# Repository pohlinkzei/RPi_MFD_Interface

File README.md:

# RPi_MFD_Interface
Interface between RaspberryPi and VW MFD Radio Navigation System

The RPi_MFD_Interface is a Atmega16-based device to connect the
RaspberryPi with the CarAudio head unit. Its main purpose is to read the
buttons of the car audio and send it to the pi.  The second purpose is
to power the pi with control over booting up and shutting down of the
raspberry pi to prevent it killing the cars battery.

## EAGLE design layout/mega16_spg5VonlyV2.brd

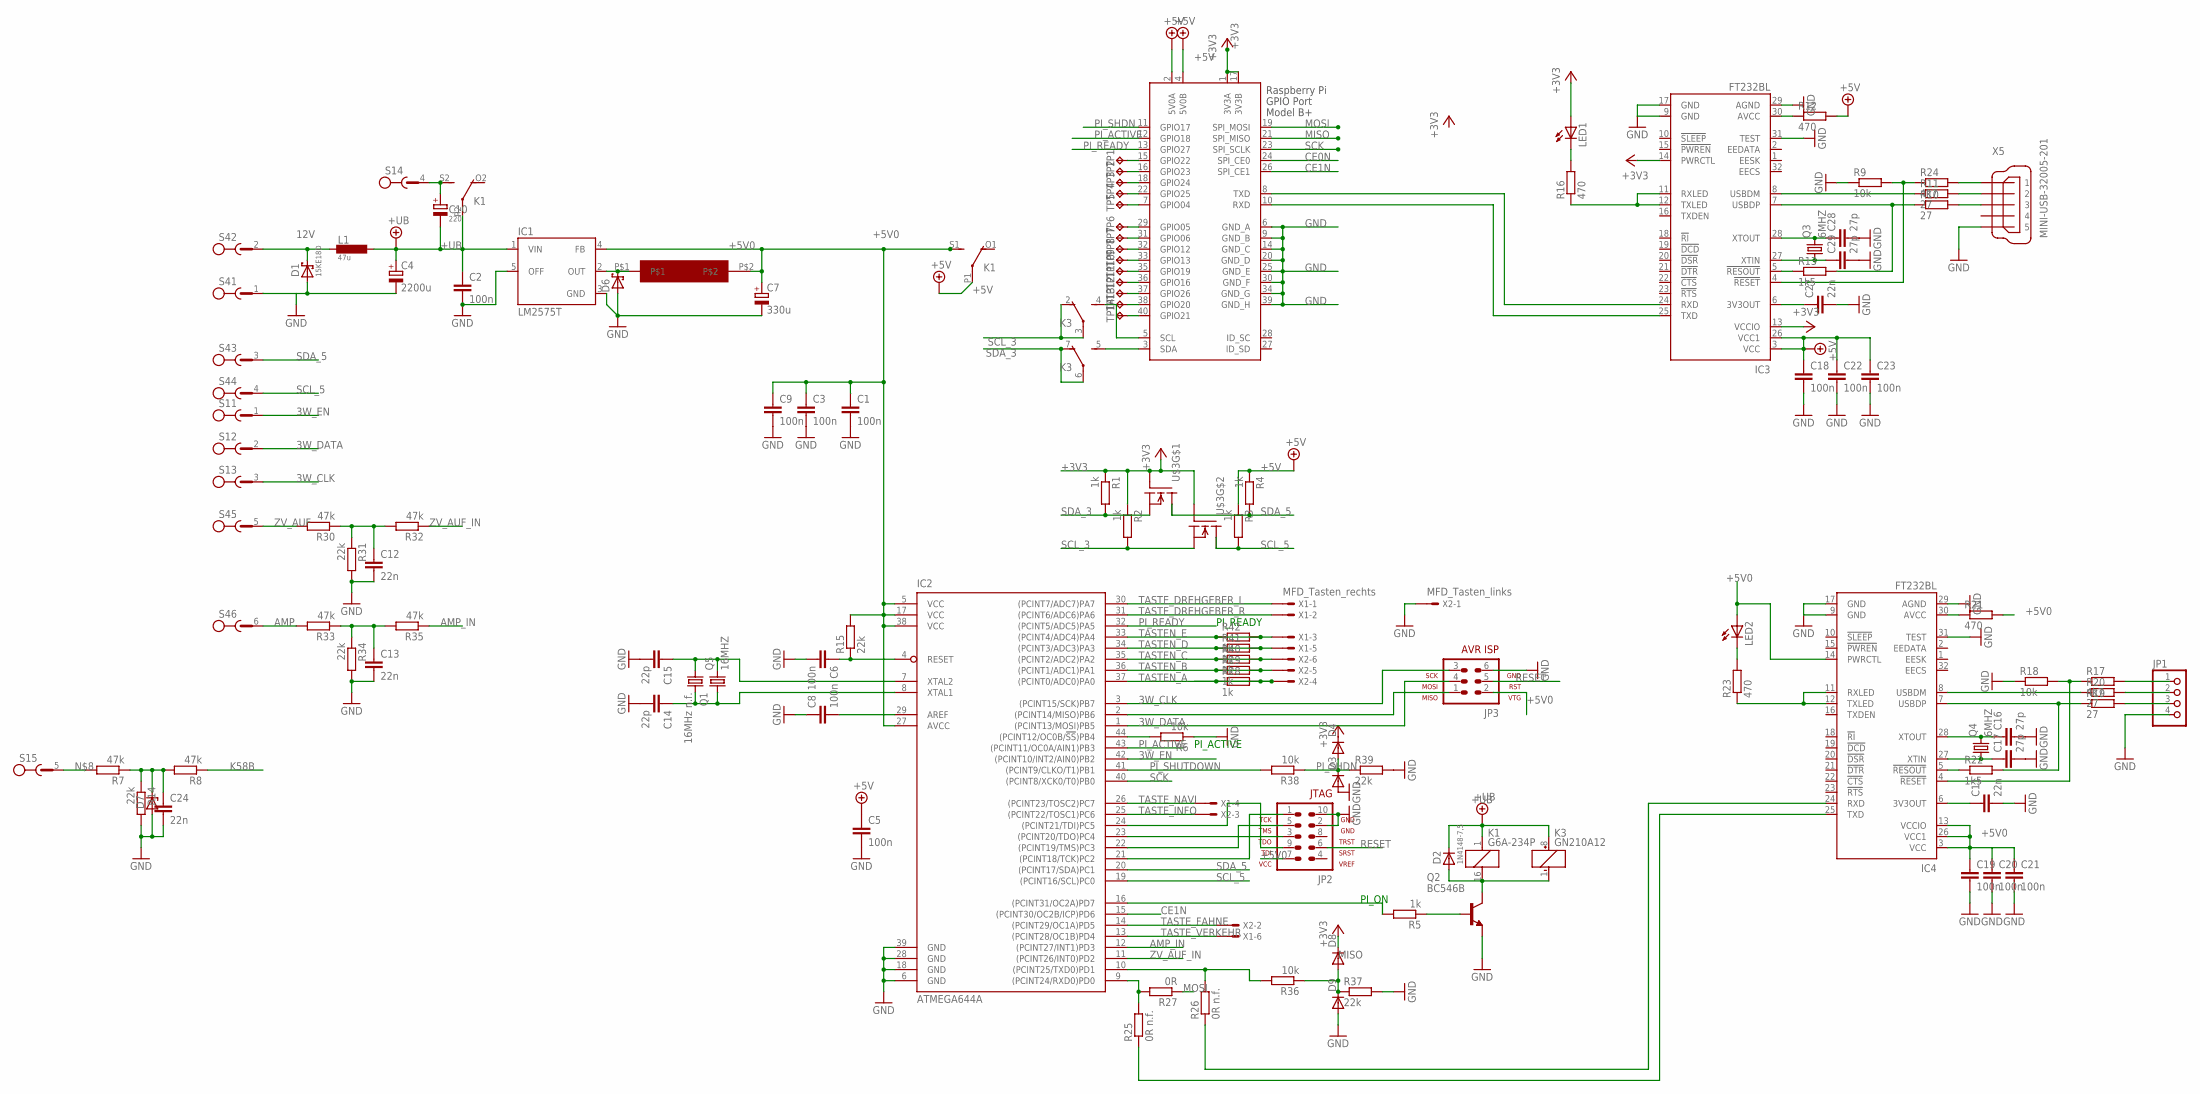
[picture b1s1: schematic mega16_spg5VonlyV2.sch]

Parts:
C1, C2, C3, C5, C6, C8, C9, C18, C19, C20, C21, C22, C23: 100n; C1206
C4: 2200u; E5-10,5
C7: 330u; E5-10,5
C10: 220; E2.5-5
C11, C12, C13, C24, C27: 22n; C1206
C14, C15: 22p; C1206
C16, C17, C28, C29: 27p; C1206
D1: 15KE18D; DO201T15
D2: 1N4148-7,5; DO35-7,5
D3, D4, D8, D9: DIODE-MICROMELF-W; MICROMELF-W
D6: SCHOTTKY-DIODEF126Z12; F126Z12
D7: ZPP-7.5; DO35-7,5
IC1: LM2575T; TO220-5
IC2: ATMEGA644A; TQFP44
IC3, IC4: FT232BL; LQFP32-7X7
JP1: PINHD-1X4_2.54; 1X04
JP2: AVR-JTAG-10
JP3: AVR-ISP-6
K1: G6A-234P
K3: GN210A12; GN-A
L1: 47u; MESC26
LED1, LED2: LEDP-LCC-2; P-LCC-2
Q1: 16MHz n.f.; HC49/S
Q2: BC546B; TO92-EBC
Q3, Q4: 6MHZ; CTS406
Q5: 16MHZ; CTS406
R1, R2, R3, R4, R5, R28, R29, R40, R41, R42: 1k; M1206
R6, R9, R18, R36, R38: 10k; M1206
R7, R8, R30, R32, R33, R35: 47k; M1206
R10, R11, R19, R20: 27; M1206
R12, R16, R21, R23: 470; M1206
R13, R22: 1k5; M1206
R14, R15, R31, R34, R37: 22k; M1206
R17, R24: 4k7; M1206
R25, R26: 0R n.f.; M1206
R27: 0R; M1206
R39: 22k; R1206
S1: CON-RIA-183-05; RIA-183-05
S4: CON-RIA-183-06; RIA-183-06
TP1, TP2, TP3, TP4, TP5, TP6, TP7, TP8, TP9, TP10, TP11, TP12, TP13, TP14: TPPAD1-13; P1-13
U$1: PISR
U$3: IRF7103; SO-8
X1: MFD_Tasten_rechts; 057-006-1
X2: MFD_Tasten_links; 057-006-1
X3: RASPI_GPIO_B+#_PIN; RASPI_GPIO_B+_PIN
X5: MINI-USB-32005-201; 32005-201

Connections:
3W_CLK: IC2.3 ((PCINT15/SCK)PB7), JP3.3, S1.3
3W_DATA: IC2.1 ((PCINT13/MOSI)PB5), JP3.4, S1.2
3W_EN: IC2.42 ((PCINT10/INT2/AIN0)PB2), S1.1
12V: D1.C, L1.1, S4.2
+3V3: D4.C, D8.C, IC3.13 (VCCIO), IC3.14 (PWRCTL), LED1.A, R1.1, R2.1, U$3.2 (G), U$3.4 (G), X3.1 (3V3A), X3.17 (3V3B)
+5V: C5.1, C18.1, C22.1, C23.1, IC3.3 (VCC), IC3.26 (VCC1), K1.P1, R3.1, R4.1, R12.2, X3.2 (5V0A), X3.4 (5V0B)
+5V0: C1.1, C3.1, C7.+, C9.1, C19.1, C20.1, C21.1, IC1.4 (FB), IC2.5 (VCC), IC2.17 (VCC), IC2.27 (AVCC), IC2.38 (VCC), IC4.3 (VCC), IC4.13 (VCCIO), IC4.14 (PWRCTL), IC4.26 (VCC1), JP2.7, JP3.2, K1.S1 (S), LED2.A, R15.2, R21.2, U$1.P$2
+UB: C2.1, C4.+, C10.-, D2.C, IC1.1 (VIN), K1.1, K1.P2, K3.8 (+), L1.2
AMP: R33.2, S4.6
AMP_IN: IC2.12 ((PCINT27/INT1)PD3), R35.1
CE0N: X3.24 (SPI_CE0)
CE1N: IC2.15 ((PCINT30/OC2B/ICP)PD6), X3.26 (SPI_CE1)
GND: C1.2, C2.2, C3.2, C4.-, C5.2, C6.2, C7.-, C8.1, C9.2, C11.2, C12.2, C13.2, C14.2, C15.2, C16.2, C17.2, C18.2, C19.2, C20.2, C21.2, C22.2, C23.2, C24.2, C27.2, C28.2, C29.2, D1.A, D3.A, D6.A, D7.A, D9.A, IC1.3 (GND), IC1.5 (OFF), IC2.6 (GND), IC2.18 (GND), IC2.28 (GND), IC2.39 (GND), IC3.9 (GND), IC3.17 (GND), IC3.29 (AGND), IC3.31 (TEST), IC4.9 (GND), IC4.17 (GND), IC4.29 (AGND), IC4.31 (TEST), JP1.4, JP2.2, JP2.10, JP3.6, Q2.E, R6.1, R9.1, R14.2, R18.1, R31.2, R34.2, R37.2, R39.2, S4.1, X2.1, X3.6 (GND_A), X3.9 (GND_B), X3.14 (GND_C), X3.20 (GND_D), X3.25 (GND_E), X3.30 (GND_F), X3.34 (GND_G), X3.39 (GND_H), X5.5
K58B: R8.1
MISO: D8.A, D9.C, R36.1, R37.1, X3.21 (SPI_MISO)
MOSI: R27.1, X3.19 (SPI_MOSI)
unnamed: C10.+, K1.S2 (S), S1.4
unnamed: D2.A, K1.16 (2), K3.1 (-), Q2.C
unnamed: IC3.24 (RXD), X3.8 (TXD)
unnamed: C24.1, D7.C, R7.1, R8.2, R14.1
unnamed: D6.C, IC1.2 (OUT), U$1.P$1
unnamed: C15.1, IC2.7 (XTAL2), Q1.1, Q5.3 (2)
unnamed: C8.2, IC2.29 (AREF)
unnamed: R7.2, S1.5
unnamed: IC3.25 (TXD), X3.10 (RXD)
unnamed: IC2.10 ((PCINT25/TXD0)PD1), R26.2, R36.2
unnamed: IC2.21 ((PCINT18/TCK)PC2), JP2.1
unnamed: IC2.22 ((PCINT19/TMS)PC3), JP2.5
unnamed: Q2.B, R5.1
unnamed: IC2.44 ((PCINT12/OC0B/!SS!)PB4), R6.2
unnamed: IC2.23 ((PCINT20/TDO)PC4), JP2.3
unnamed: IC2.16 ((PCINT31/OC2A)PD7), R5.2
unnamed: IC2.24 ((PCINT21/TDI)PC5), JP2.9
unnamed: C11.1, IC4.6 (3V3OUT)
unnamed: IC3.11 (RXLED), IC3.12 (TXLED), R16.1
unnamed: IC2.2 ((PCINT14/MISO)PB6), JP3.1
unnamed: LED1.C, R16.2
unnamed: IC4.7 (USBDP), R19.1, R22.2
unnamed: IC4.8 (USBDM), R20.1
unnamed: JP1.1, R17.2
unnamed: IC4.4 (!RESET), R17.1, R18.2
unnamed: JP1.3, R19.2
unnamed: JP1.2, R20.2
unnamed: IC4.30 (AVCC), R21.1
unnamed: IC4.5 (!RESOUT), R22.1
unnamed: C17.1, IC4.27 (XTIN), Q4.1
unnamed: C16.1, IC4.28 (XTOUT), Q4.3 (2)
unnamed: IC4.24 (RXD), R26.1
unnamed: IC4.25 (TXD), R25.1
unnamed: IC4.11 (RXLED), IC4.12 (TXLED), R23.1
unnamed: LED2.C, R23.2
unnamed: IC2.9 ((PCINT24/RXD0)PD0), R25.2, R27.2
unnamed: K3.5 (S), X3.3 (SDA)
unnamed: TP14.1, X3.40 (GPIO21)
unnamed: K3.4 (S), X3.5 (SCL)
unnamed: TP13.1, X3.38 (GPIO20)
unnamed: TP12.1, X3.37 (GPIO26)
unnamed: TP11.1, X3.36 (GPIO16)
unnamed: TP10.1, X3.35 (GPIO19)
unnamed: TP9.1, X3.33 (GPIO13)
unnamed: C14.1, IC2.8 (XTAL1), Q1.2, Q5.1
unnamed: TP8.1, X3.32 (GPIO12)
unnamed: TP7.1, X3.31 (GPIO06)
unnamed: TP6.1, X3.29 (GPIO05)
unnamed: TP1.1, X3.15 (GPIO22)
unnamed: C12.1, R30.1, R31.1, R32.2
unnamed: TP2.1, X3.16 (GPIO23)
unnamed: C13.1, R33.1, R34.1, R35.2
unnamed: TP3.1, X3.18 (GPIO24)
unnamed: R10.2, X5.3
unnamed: R11.2, X5.2
unnamed: IC3.30 (AVCC), R12.1
unnamed: IC3.5 (!RESOUT), R13.1
unnamed: C27.1, IC3.6 (3V3OUT)
unnamed: IC3.7 (USBDP), R10.1, R13.2
unnamed: IC3.8 (USBDM), R11.1
unnamed: R24.2, X5.1
unnamed: IC3.4 (!RESET), R9.2, R24.1
unnamed: C29.1, IC3.27 (XTIN), Q3.1
unnamed: C28.1, IC3.28 (XTOUT), Q3.3 (2)
unnamed: TP4.1, X3.22 (GPIO25)
unnamed: TP5.1, X3.7 (GPIO04)
PI_ACTIVE: IC2.43 ((PCINT11/OC0A/AIN1)PB3), X3.12 (GPIO18)
PI_READY: IC2.32 ((PCINT5/ADC5)PA5), X3.13 (GPIO27)
PI_SHDN: D3.C, D4.A, R38.1, R39.1, X3.11 (GPIO17)
PI_SHUTDOWN: IC2.41 ((PCINT9/CLKO/T1)PB1), R38.2
RESET: C6.1, IC2.4 (RESET), JP2.6, JP3.5, R15.1
SCK: IC2.40 ((PCINT8/XCK0/T0)PB0), X3.23 (SPI_SCLK)
SCL_3: K3.2 (O), K3.3, R2.2, U$3.3 (S)
SCL_5: IC2.19 ((PCINT16/SCL)PC0), R3.2, S4.4, U$3.5 (D1), U$3.6 (D)
SDA_3: K3.6, K3.7 (O), R1.2, U$3.1 (S)
SDA_5: IC2.20 ((PCINT17/SDA)PC1), R4.2, S4.3, U$3.7 (D), U$3.8 (D1)
TASTEN_A: IC2.37 ((PCINT0/ADC0)PA0), R28.1, R28.2, X2.4
TASTEN_B: IC2.36 ((PCINT1/ADC1)PA1), R29.1, R29.2, X2.5
TASTEN_C: IC2.35 ((PCINT2/ADC2)PA2), R40.1, R40.2, X2.6
TASTEN_D: IC2.34 ((PCINT3/ADC3)PA3), R41.1, R41.2, X1.5
TASTEN_E: IC2.33 ((PCINT4/ADC4)PA4), R42.1, R42.2, X1.3
TASTE_DREHGEBER_L: IC2.30 ((PCINT7/ADC7)PA7), X1.1
TASTE_DREHGEBER_R: IC2.31 ((PCINT6/ADC6)PA6), X1.2
TASTE_FAHNE: IC2.14 ((PCINT29/OC1A)PD5), X2.2
TASTE_INFO: IC2.25 ((PCINT22/TOSC1)PC6), X2.3
TASTE_NAVI: IC2.26 ((PCINT23/TOSC2)PC7), X1.4
TASTE_VERKEHR: IC2.13 ((PCINT28/OC1B)PD4), X1.6
ZV_AUF: R30.2, S4.5
ZV_AUF_IN: IC2.11 ((PCINT26/INT0)PD2), R32.1

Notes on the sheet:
PI_ACTIVE
PI_ON
PI_READY

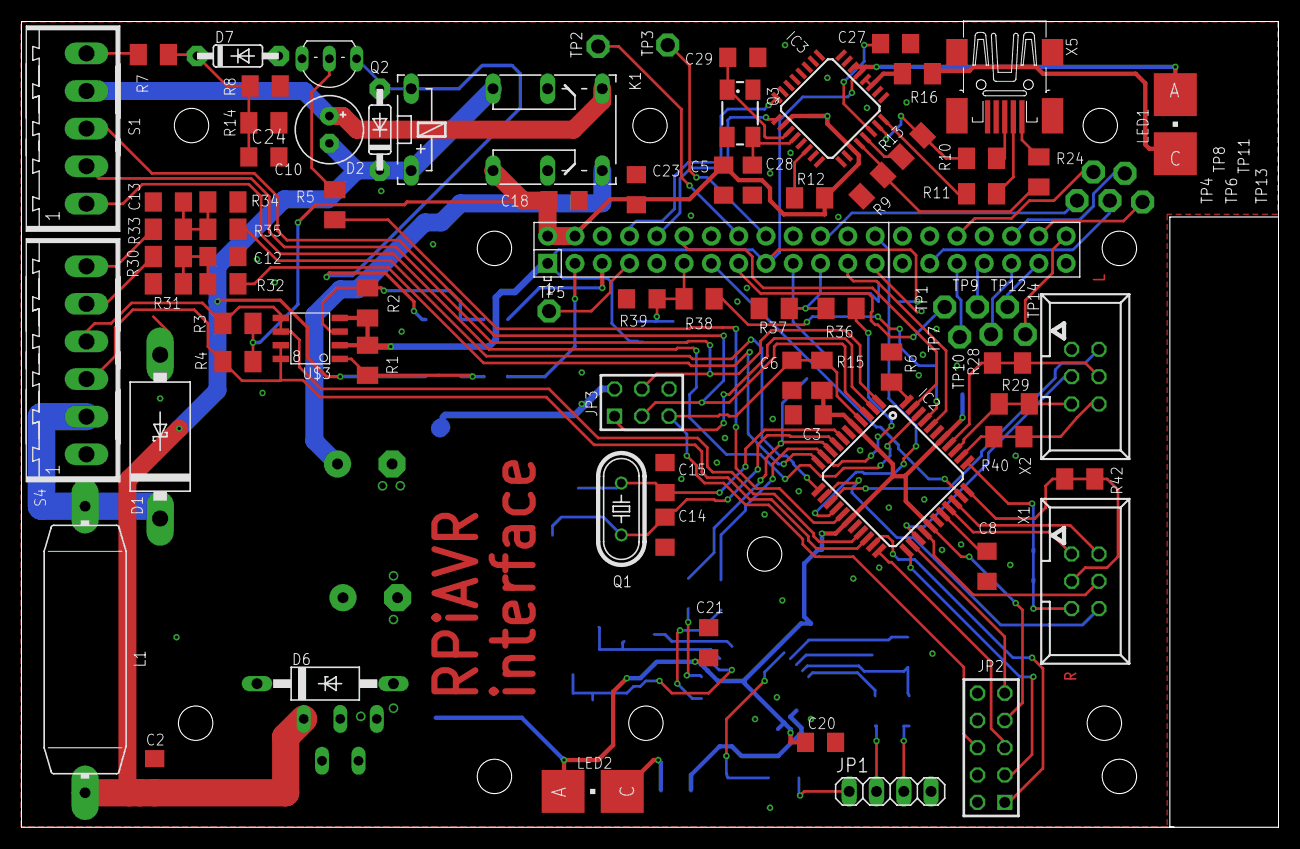
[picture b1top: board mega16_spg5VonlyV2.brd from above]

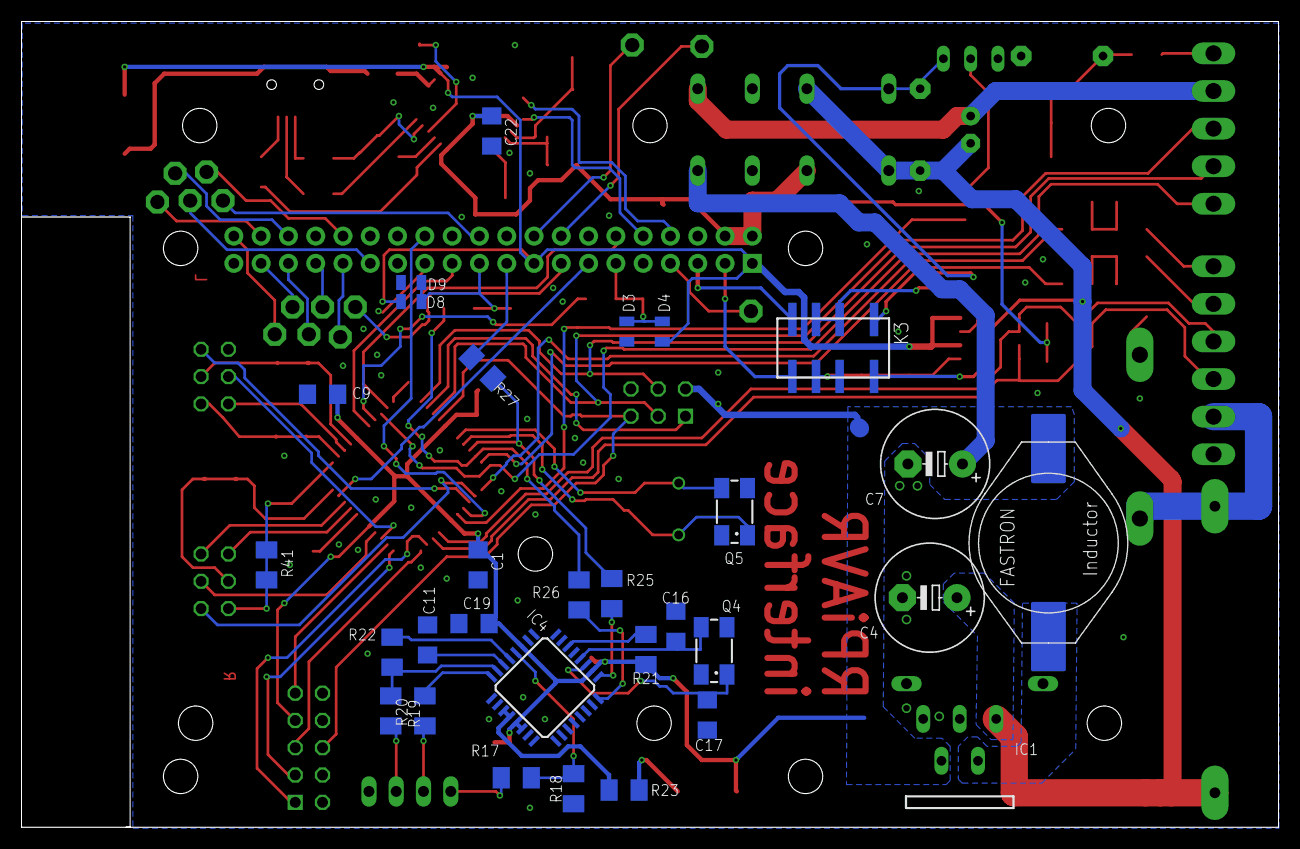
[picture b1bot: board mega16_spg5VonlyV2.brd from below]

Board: 2 copper layers, 117.0 x 75.0 mm, 117 parts (30 on the bottom side), 103 nets.

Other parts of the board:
U$2: EUROBOX

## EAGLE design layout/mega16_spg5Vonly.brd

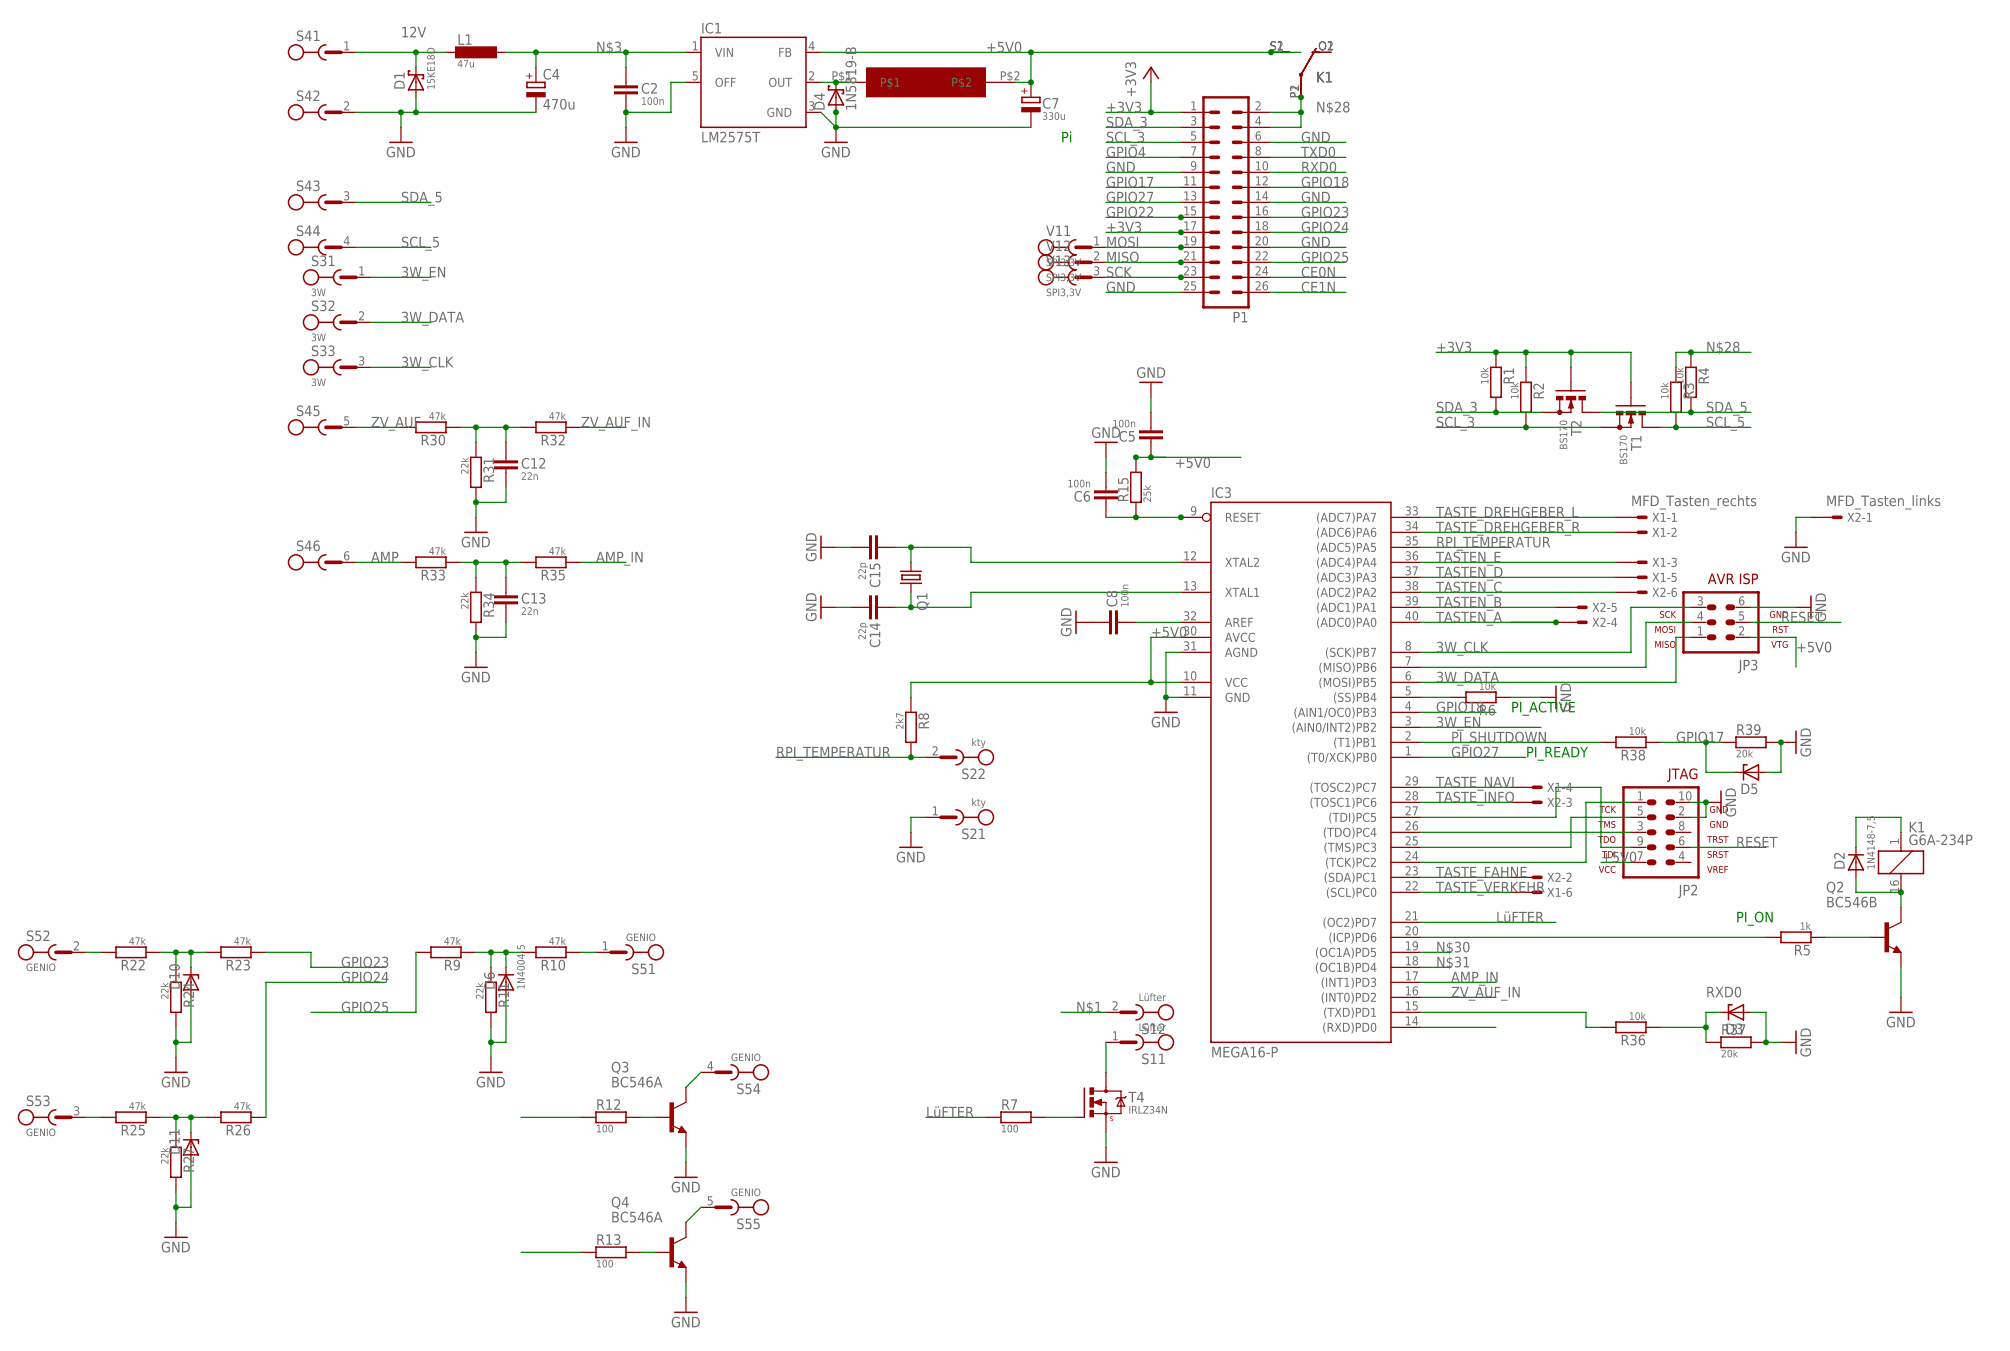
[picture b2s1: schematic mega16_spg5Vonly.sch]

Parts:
C2, C5, C6, C8: 100n; C_50_SCHMAL
C4: 470u; E5-10,5
C7: 330u; E5-10.5
C12, C13: 22n; C_50_SCHMAL
C14, C15: 22p; C_50_SCHMAL
D1: 15KE18D; DO201T15
D2: 1N4148-7,5; DO35-7,5
D3, D5, D10, D11: ZPP-7.5; DO35-7,5
D4: 1N5819-B; DO41-7.6
D6: 1N4004-5; DO41-5
IC1: LM2575T; TO220-5
IC3: MEGA16-P; DIL40
JP2: AVR-JTAG-10
JP3: AVR-ISP-6
K1: G6A-234P
L1: 47u; MESC26
P1: ML26
Q1: CRYSTALHC49S; HC49/S
Q2: BC546B; TO92-EBC
Q3, Q4: BC546A; TO92-EBC
R1, R2, R3, R4, R6, R36, R38: 10k; R_10
R5: 1k; R_10
R7, R12, R13: 100; R_10
R8: 2k7; R_10
R9, R10, R22, R23, R25, R26, R30, R32, R33, R35: 47k; R_10
R11, R24, R27, R31, R34: 22k; R_10
R15: 25k; R_10
R37, R39: 20k; R_10
S1: Lüfter; CON-PLATINE_2-POLIG-GERADE
S2: kty; CON-PLATINE_2-POLIG-GERADE
S3: 3W; RIA-183-03
S4: CON-RIA-183-06; RIA-183-06
S5: GENIO; CON-PLATINE_5-POLIG
T1, T2: BS170; SOT54E
T4: IRLZ34N; TO220BV
U$1: PISR
V1: SPI3,3V; CON-PLATINE_3-POLIG-GERADE
X1: MFD_Tasten_rechts; 057-006-1
X2: MFD_Tasten_links; 057-006-1

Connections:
3W_CLK: IC3.8 ((SCK)PB7), JP3.3, S3.3
3W_DATA: IC3.6 ((MOSI)PB5), JP3.1, S3.2
3W_EN: IC3.3 ((AIN0/INT2)PB2), S3.1
12V: D1.C, L1.1, S4.1
+3V3: P1.1, P1.17, R1.1, R2.1, T1.G, T2.G
+5V0: C5.1, C7.+, IC1.4 (FB), IC3.10 (VCC), IC3.30 (AVCC), JP2.7, JP3.2, K1.S1 (S), K1.S2 (S), R8.1, R15.2, U$1.P$2
AMP: R33.2, S4.6
AMP_IN: IC3.17 ((INT1)PD3), R35.1
CE0N: P1.24, R12.1
CE1N: P1.26, R13.1
GND: C2.2, C4.-, C5.2, C6.2, C7.-, C8.1, C12.2, C13.2, C14.2, C15.2, D1.A, D3.A, D4.A, D5.A, D6.A, D10.A, D11.A, IC1.3 (GND), IC1.5 (OFF), IC3.11 (GND), IC3.31 (AGND), JP2.2, JP2.10, JP3.6, P1.6, P1.9, P1.14, P1.20, P1.25, Q2.E, Q3.E, Q4.E, R6.1, R11.2, R24.2, R27.2, R31.2, R34.2, R37.2, R39.2, S2.1, S4.2, T4.S, X2.1
GPIO4: P1.7
GPIO17: D5.C, P1.11, R38.1, R39.1
GPIO18: IC3.4 ((AIN1/OC0)PB3), P1.12
GPIO22: P1.15
GPIO23: P1.16, R23.1
GPIO24: P1.18, R26.1
GPIO25: P1.22, R9.2
GPIO27: IC3.1 ((T0/XCK)PB0), P1.13
LüFTER: IC3.21 ((OC2)PD7), R7.1
MISO: P1.21, V1.2
MOSI: P1.19, V1.1
unnamed: D2.A, K1.16 (2), Q2.C
unnamed: C2.1, C4.+, D2.C, IC1.1 (VIN), K1.1, L1.2
unnamed: R7.2, T4.G
unnamed: D4.C, IC1.2 (OUT), U$1.P$1
unnamed: C15.1, IC3.12 (XTAL2), Q1.1
unnamed: C8.2, IC3.32 (AREF)
unnamed: S1.1, T4.D
unnamed: D6.C, R9.1, R10.2, R11.1
unnamed: IC3.15 ((TXD)PD1), R36.2
unnamed: IC3.24 ((TCK)PC2), JP2.1
unnamed: IC3.25 ((TMS)PC3), JP2.5
unnamed: Q2.B, R5.1
unnamed: IC3.5 ((SS)PB4), R6.2
unnamed: IC3.26 ((TDO)PC4), JP2.3
unnamed: IC3.20 ((ICP)PD6), R5.2
unnamed: IC3.27 ((TDI)PC5), JP2.9
unnamed: Q4.C, S5.5
unnamed: Q3.C, S5.4
unnamed: IC3.7 ((MISO)PB6), JP3.4
unnamed: R22.2, S5.2
unnamed: R25.2, S5.3
unnamed: D10.C, R22.1, R23.2, R24.1
unnamed: D11.C, R25.1, R26.2, R27.1
unnamed: Q3.B, R12.2
unnamed: R10.1, S5.1
unnamed: Q4.B, R13.2
unnamed: K1.P1, K1.P2, P1.2, P1.4, R3.1, R4.1
unnamed: K1.O1 (O), K1.O2 (O)
unnamed: C14.1, IC3.13 (XTAL1), Q1.2
unnamed: C12.1, R30.1, R31.1, R32.2
unnamed: C13.1, R33.1, R34.1, R35.2
PI_SHUTDOWN: IC3.2 ((T1)PB1), R38.2
RESET: C6.1, IC3.9 (RESET), JP2.6, JP3.5, R15.1
RPI_TEMPERATUR: IC3.35 ((ADC5)PA5), R8.2, S2.2
RXD0: D3.C, P1.10, R36.1, R37.1
SCK: P1.23, V1.3
SCL_3: P1.5, R2.2, T1.S
SCL_5: R3.2, S4.4, T1.D
SDA_3: P1.3, R1.2, T2.S
SDA_5: R4.2, S4.3, T2.D
TASTEN_A: IC3.40 ((ADC0)PA0), X2.4
TASTEN_B: IC3.39 ((ADC1)PA1), X2.5
TASTEN_C: IC3.38 ((ADC2)PA2), X2.6
TASTEN_D: IC3.37 ((ADC3)PA3), X1.5
TASTEN_E: IC3.36 ((ADC4)PA4), X1.3
TASTE_DREHGEBER_L: IC3.33 ((ADC7)PA7), X1.1
TASTE_DREHGEBER_R: IC3.34 ((ADC6)PA6), X1.2
TASTE_FAHNE: IC3.23 ((SDA)PC1), X2.2
TASTE_INFO: IC3.28 ((TOSC1)PC6), X2.3
TASTE_NAVI: IC3.29 ((TOSC2)PC7), X1.4
TASTE_VERKEHR: IC3.22 ((SCL)PC0), X1.6
TXD0: IC3.14 ((RXD)PD0), P1.8
ZV_AUF: R30.2, S4.5
ZV_AUF_IN: IC3.16 ((INT0)PD2), R32.1

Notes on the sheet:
PI_READY
PI_ACTIVE
PI_ON

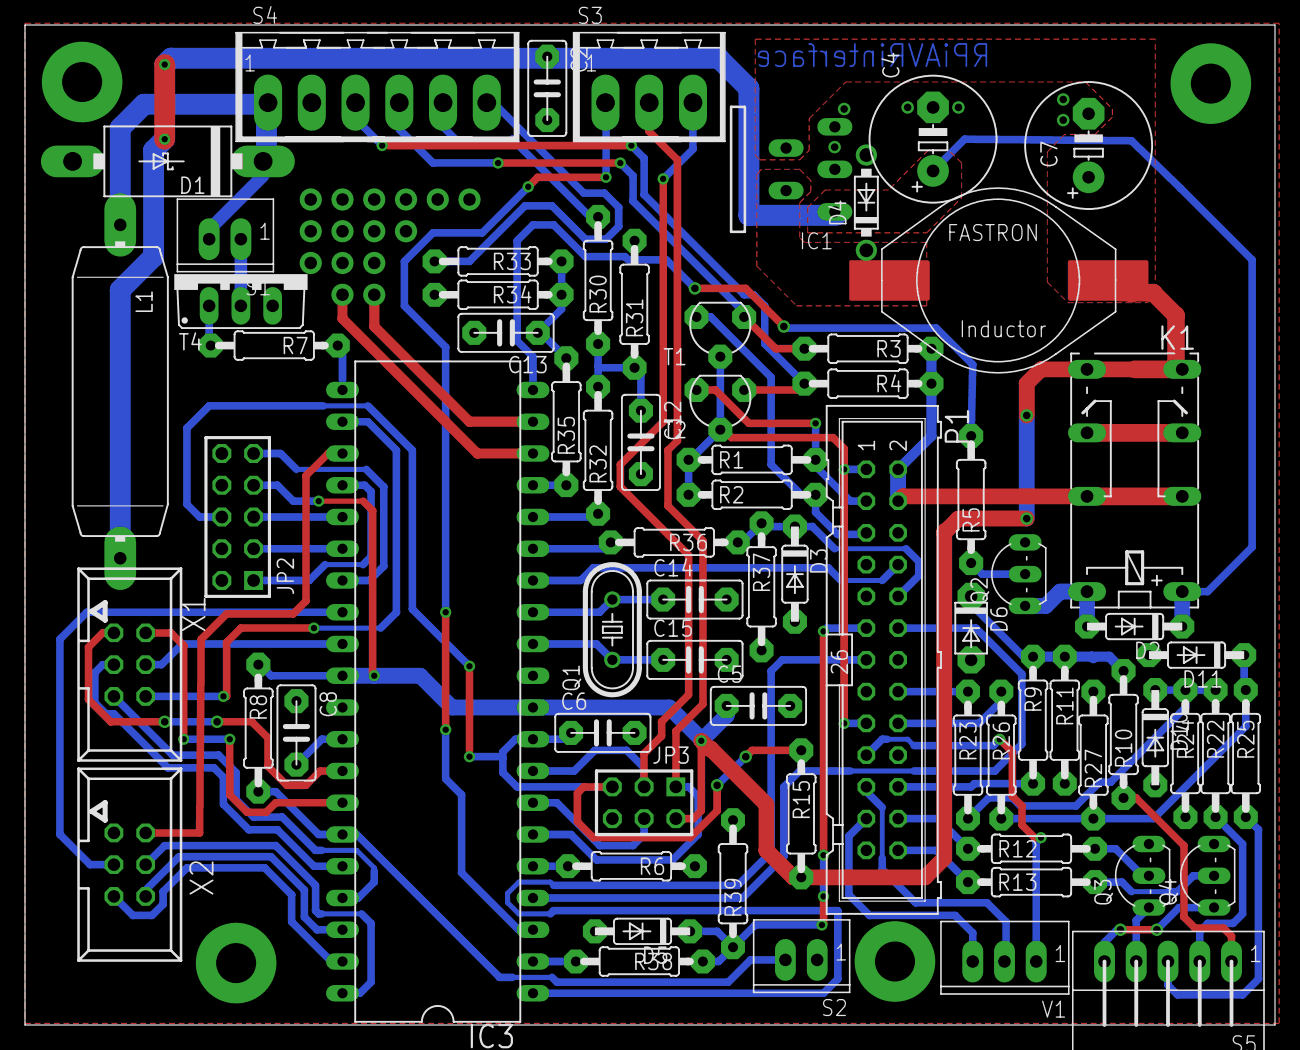
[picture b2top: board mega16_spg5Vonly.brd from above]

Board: 2 copper layers, 100.0 x 80.0 mm, 71 parts (0 on the bottom side), 74 nets.

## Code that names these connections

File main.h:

#ifndef MAIN_H
#define MAIN_H
#ifndef F_CPU
#define F_CPU 16000000UL
#endif
#include <avr/io.h>
#include <stdbool.h>
#include <util/delay.h>
#include <avr/sleep.h>
#include <avr/interrupt.h>

// 3LB
#define PORT_3LB PORTB	
#define DDR_3LB	DDRB
#define EN		PB2 //INT2
#define DATA	PB5 //MOSI
#define CLK		PB7 //SCK
#define AUX		1
#define NOT_AUX	0
#define AUX_INFO 2
#define AUX_NR 3

// Shutdown Pi
#define PIPORT PORTB
#define PIPIN PINB
#define PIDDR DDRB
#define PIACTIVE PB3
#define PISHUTDOWN PB1
#define PIREADY PB0

// Start Pi
#define PISTARTPDDR DDRD
#define PISTARTPORT PORTD
#define PISTART PD6 

#define ZV_PIN	PIND
#define ZV_ZU	PD2

#define AMP_PIN PIND
#define AMP_ON PD3

// cool Pi
#define PWM OCR2
#define PWM_HIGH 255
#define PWM_MED	128
#define PWM_LOW	64
#define PWM_OFF 0
#define TEMP_HIGH 350
#define TEMP_MED 300
#define TEMP_LOW 275
#define PI_TEMP PA5

#define TIMEOUT_10MIN 600 //10 min (100ms * 600)

uint8_t read_3lb(void);

extern volatile uint16_t pi_shutdown_count;
extern volatile uint16_t pi_start_count;
extern volatile uint8_t data_3lb[20];
extern volatile bool status;
extern uint8_t count_3lb;
extern volatile uint32_t spi_timeout;

#endif

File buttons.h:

#ifndef BUTTONS_H
#define BUTTONS_H


#include <avr/io.h>
#include <stdbool.h>
#include <string.h>
#include "adc.h"

// MFD Buttons
#define BUTTON_DDR DDRC
#define BUTTON_PORT PORTC
#define BUTTON_PIN PINC
#define BUTTON_NAVI PC7
#define BUTTON_FAHNE PD5
#define BUTTON_INFO PC6
#define BUTTON_VERKEHR PD4
#define BUTTONS_A PA0
#define BUTTONS_B PA1
#define BUTTONS_C PA2
#define BUTTONS_D PA3
#define BUTTONS_E PA4

	// 3,3V 168 153 - 183
	// 2,6V 133 118 - 148
	// 1,8V 92 107 - 137
	// 0,9V 46 31 - 61

#define UPPER3V3 183
#define LOWER3V3 153
#define UPPER2V6 148
#define LOWER2V6 118
#define UPPER1V8 107
#define LOWER1V8 77
#define UPPER0V9 61
#define LOWER0V9 31
#define UPPER0V0 25

typedef struct but{
	bool next;
	bool prev;
	bool eject;
	bool tim;
	bool info;
	bool as;
	bool scan;
	bool _1;
	bool _2;
	bool _3;
	bool flag;
	bool light;
	bool navi;
	bool back;
	bool audio;
	bool tone;
	int8_t left_right;
	bool enter;
	bool _4;
	bool _5;
	bool _6;
	bool traffic;
}buttons_t;


extern volatile buttons_t buttons, buttons_old;

void buttons_init(void);
void buttons_task(void);

#endif

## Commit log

2015-08-28 :space_invader: Added .gitattributes
2015-08-28 Initial commit
    The RPi_MFD_Interface is a Atmega16-based device to connect the
    RaspberryPi with the CarAudio head unit. Its main purpose is to read the
    buttons of the car audio and send it to the pi. The second purpose is
    to power the pi with control over booting up and shutting down of the
    raspberry pi to prevent it killing the cars battery.
2015-08-28 Add: Layout
2015-08-28 Fix: SPI-Connection
2015-10-28 update: change to device tree overlay for the raspberry pi
2015-11-05 Minor fixes
2015-11-05 remove unused file
2015-11-07 fix: magic restart
2015-11-14 fix and update
2015-11-22 code cleanup
2015-11-23 update: use sleepmode and central locking
2015-12-02 update: make rotary encode faster
2016-01-13 nope
2016-01-13 fix merge
2016-01-13 fix typo
2016-01-15 improve rotary code
2016-05-24 add restart button
2018-04-19 Align to new HW version 2
2018-04-19 add a do not start flag
2018-04-19 Add HW design
2019-12-05 add timeout to zv to prevnt power waste when radio is off but zv is open
